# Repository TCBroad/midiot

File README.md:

# midiot
Application for sending a list of midi commands when a midi message is received

Currently windows only - .netcore3.1 with WPF. If that comes to other platforms then it'd probably work.

The binary on the releases page is a self-contained .net executable (hence the size) so you shouldn't have to install any dependencies.

## File format
[label] command command command ... 

## Command types
- CHn - Set channel for subsequent commands to n
- PCn - Send program change 'n'
- CCn,v - Send control change number 'n' value 'v'

### Example file

\[intro\]CH2 PC12\
\[harmony\]PC0 CC34,1\
\[riffs\]CC34,0\
\[clean\]PC12\
\[riffs\]CC34,0\
\[clean\]PC12\
\[solo\]PC0 CC34,1\
\[riffs\]CC34,0

The midi channel only needs setting once until you want to change it

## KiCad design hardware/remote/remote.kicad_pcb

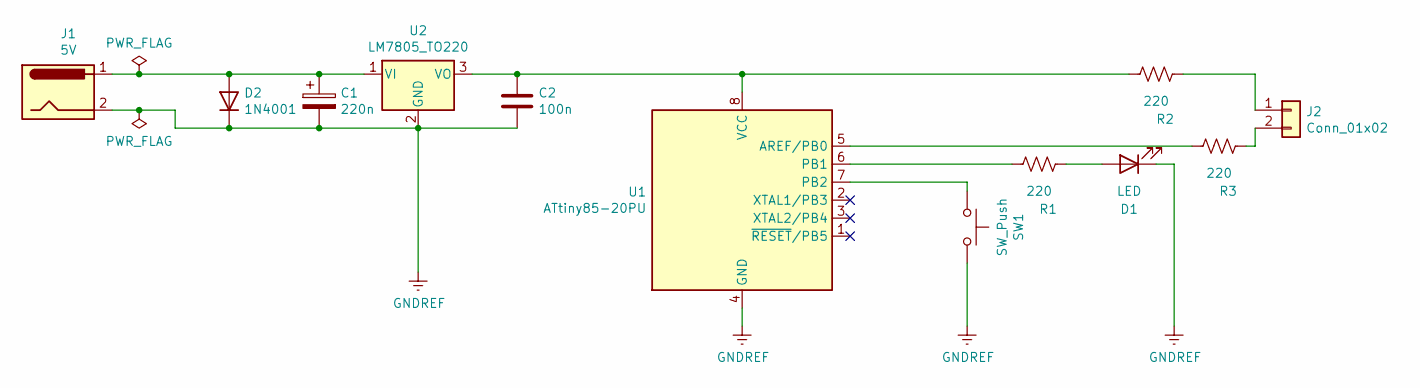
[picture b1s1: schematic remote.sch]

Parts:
C1: 220n; CP_Radial_D5.0mm_P2.50mm
C2: 100n; C_Disc_D6.0mm_W2.5mm_P5.00mm
D1: LED; LED_D5.0mm
D2: 1N4001; D_DO-41_SOD81_P10.16mm_Horizontal
J1: 5V; PinHeader_2x01_P2.54mm_Vertical
J2: Conn_01x02; PinHeader_2x01_P2.54mm_Vertical
R1, R2, R3: 220; R_Axial_DIN0207_L6.3mm_D2.5mm_P7.62mm_Horizontal
SW1: SW_Push; PinHeader_2x01_P2.54mm_Vertical
U1: ATtiny85-20PU; DIP-8_W7.62mm
U2: LM7805_TO220; TO-220-3_Vertical

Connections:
GNDREF: C1.2, C2.2, D1.1 (K), D2.1 (K), J1.2, SW1.2, U1.4 (GND), U2.2 (GND)
unnamed: C1.1, D2.2 (A), J1.1, U2.1 (VI)
unnamed: C2.1, R2.2, U1.8 (VCC), U2.3 (VO)
unnamed: D1.2 (A), R1.1
unnamed: J2.1, R2.1
unnamed: J2.2, R3.1
unnamed: R1.2, U1.6 (PB1)
unnamed: R3.2, U1.5 (AREF/PB0)
unnamed: SW1.1, U1.7 (PB2)

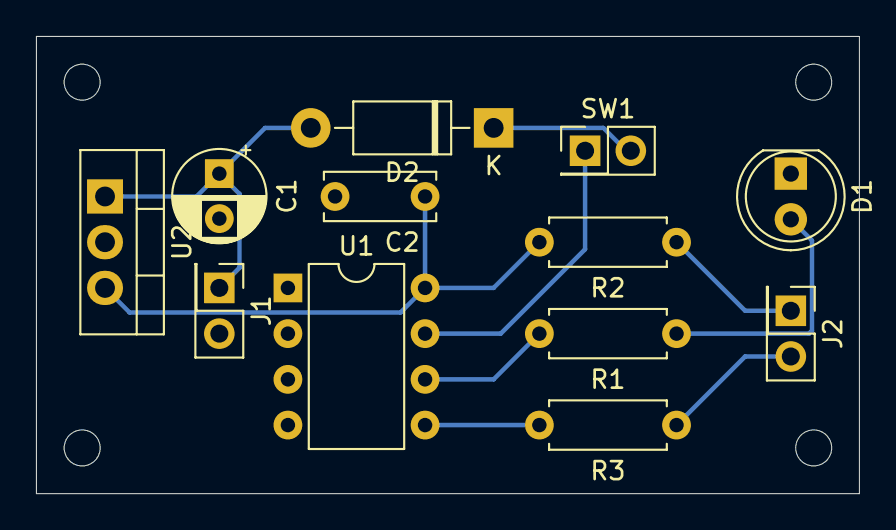
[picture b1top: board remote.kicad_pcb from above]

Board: 2 copper layers, 45.7 x 25.4 mm, 12 parts (0 on the bottom side), 9 nets.

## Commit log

2021-02-06 [app] Initial working version completed
2021-02-06 [docs] Added basic readme
2021-02-06 [docs] Updated readme
2021-02-07 [app] Forced single-instance, updated list view layout
2021-04-22 [firmware] Added initial firmware for remote
2021-04-22 [app] Small UI updates
2021-04-22 [hardware] Added schematics and pcb layout for remote
2021-04-22 [hardware] Improved PCB layout
